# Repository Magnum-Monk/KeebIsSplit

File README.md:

### Keeb Is Split

#### Whats the big idea? (TLDR)
Robust, decent-looking, comfortable, cost-effective, easy-to-build/repair/use 3x6 split keyboard. 

#### References / Credits / Inspirations :
- [**CRKBD**](https://github.com/foostan/crkbd) - all-time classic, "industry standart" of DIY ergo keyboards at this point, if I could say so myself;
- [**Cantor/Piantor**](https://github.com/diepala/cantor) - excellent thumb cluster, overall big improvement in layout ergonimics imo.
- [**Altair/Altair-X**](https://www.reddit.com/r/MechanicalKeyboards/comments/1cg4ejp/gb_altairx_live_now_a_premium_easy_to_learn/) - top grade aestethics, build quality.
- [**Cheapino**](https://github.com/tompi/cheapino) - Robust, easy to assemble, easy to fix/repair, easy to source components, well... cheap! ☺️

#### Firmware
This build utilizes exact pinout that **CRKBD** uses. So you can safely use your Corne (v2/v3) firmware to flash this keyboard.
If you've never had a Corne keyboard before, [this](https://github.com/fathulfahmy/corne-keyboard/tree/main/firmware) should work

#### Build guide 
[here](https://github.com/Magnum-Monk/KeebIsSplit/blob/main/DOC/build_guide.md)

#### BOM
| Part                 | Amount | Links                                                                                                                                                                                                                                                                                                                                                    |
|----------------------|--------|----------------------------------------------------------------------------------------------------------------------------------------------------------------------------------------------------------------------------------------------------------------------------------------------------------------------------------------------------------|
| ProMicro-like MCU    | 2      | [aliexpress](https://aliexpress.com/item/1005004242820623.html?spm=a2g2w.orderdetail.0.0.460d4aa6AvOP5C&sku_id=12000028500661497)                                                                                                                                                                                                            |
| PCB                  | 2      | JLCPCB, PCBWay or other service that you prefer                                                                                                                                                                                                                                                                                                          |
| MX HotSwap Socket    | 42     | [aliexpress](https://aliexpress.com/wholesale?SearchText=kailh+mx+socket&g=y&page=1&searchInfo=A6ON%2FDUCyFd0j2HDxpeVKVoOMc2j+7O64tYNu5a8P+V8gMksvBOiUL7krwlUwZ266w1Qflck+JXe18xAFwbaMovdHjI2%2F2ouiiGyMe3C3O8S2CPD%2Fw7SRsXFQPxfUhNKvHtfjXIBBqE1jemlzqPQiXWU4ihS99yHB8lfgTvQgW8j1PY5epuYAnrB)                                                                          |
| SMD SOD123 Diode     | 42     | [aliexpress](https://www.aliexpress.com/w/wholesale-sod-123-1n4148.html?spm=a2g0o.detail.auto_suggest.3.49e124bT24bTMs)                                                                                                                                                                                                                                       |
| USB-A Socket         | 2      | [aliexpress](https://aliexpress.com/item/1005006501690133.html?sku_id=12000037434446990&spm=a2g2w.productlist.search_results.12.5a9f44b6SVPu5b)                                                                                                                                                                                                                         |
| USB-A -> USB-A Cable | 1      | [aliexpress 1](https://aliexpress.com/item/1005003574732583.html?spm=a2g2w.orderdetail.0.0.44344aa6HsNdnS&sku_id=12000026341806398) [aliexpress 2](https://aliexpress.com/item/1005006002851777.html?spm=a2g2w.orderdetail.0.0.312e4aa6oU8xds&sku_id=12000035266036584)  [aliexpress 3](https://aliexpress.com/item/1005007351594401.html?spm=a2g2w.orderdetail.0.0.4f0d4aa6ib4thb&sku_id=12000040385973360)     |
| Reset Button         | 2      | [aliexpress](https://aliexpress.com/item/1005007177692594.html?sku_id=12000039712603251&spm=a2g2w.productlist.search_results.11.2bad61e4nLrZqG)                                                                                                                                                                                                                         |
| Header Pin Sockets (20 pin)    | 4      | [aliexpress](https://aliexpress.com/item/1005005104952508.html?sku_id=12000031676025007&spm=a2g2w.productlist.search_results.13.42b445bb9N34Mz)                                                                                                                                                                                                                         |
| M2x5 screw           | 20     | For attaching mounting plate and bottom case                                                                                                                                                                                                                                                                                                                                                         |
| M2x6 screw           | 8      | For attaching top case to bottom case |
| M2x5 spacer          | 18     | [aliexpress](https://aliexpress.com/item/4000314663724.html?sku_id=10000001297126740&spm=a2g2w.productlist.search_results.0.67825d52ElIZ9D)                                                                                                                                                                                                                             |
| Top case left           | 1      | |
| Top case right          | 1      | |
| Bottom case left        | 1      | |
| Bottom case right       | 1      | |
| Mounting plate left     | 1      | |
| Mounting plate right    | 1      | |
| Foam mid                | 2      | |
| Foam bottom             | 2      | |

#### "Why won't you just use one of those referenced options?"
(Basically, a list of nit-picks 😀 )
- **CRKBD** - thumb cluster, specifically 1.5u outermost keys. Not only does it feel a bit clunky for me to use, but also, finding matching keycaps for those keys could be challenging and annoying (and convex 1.5u spacebar is a rarity of its own kind). Although I do somewhat understand the reasoning behind this (design-wise, it makes sense to extend this key to 1.5u, because with 1u you kind of have this "weird" empty corner between this key and the MCU, which for some may look off-putting. Since the mcu is quite wide, you cannot eliminate this issue without moving the whole cluster outwards or rotating it in a werid position, which in and of itself could hurt comfort of use. TRRS connection between two halves.
> Since TRRS safety is quite sensitive and reoccuring topic in the DIY-keyboards community I will not touch it here (or will I?), but I would avoid this option if possible.

- **Cantor / Piantor** - although it is very comfortable to use layout-wise, the MCU board itself is huge, albeit much easier to flash. Which in turn somewhat leaves it with the only option for the halves connection to also be TRRS.
- **Altair/Altair-X** - Not open source. Difficult to repair, if something "dies".  Good luck finding available one to buy these days 😀, not to mention hefty price tag.
- **Cheapino** - RJ45 might be too janky-looking and overall big connector for some users (me included), Otherwise very cool and build-friendly board 🥰.

#### Why not low-profile?

Well, mostly the switches. I am yet to find LP switch, that can compete in typing feel with some remarkable and widely loved MX-type ones. And I have tried almost all chocs, a variety of KS33 and Kailh LP models. The available selection of MX switches at this point is far more superior imo, and could fulfill the needs of any enthusiast. 

#### Why not wireless?
I've tried multiple wireless keyboards, and keeping their charge levels in check is just another hassle for me. And the batteries themselves being another point of failure (experienced quite a few "spicy pillows" myself), which defeats the goal of this being robust. Maybe in the future I'll rethink this, but with the use of 3.7v AAA or coin cell batteries as a power source.

#### Why no LEDs?
I mean... Nothing against it, but it adds nothing of value to the device imo, except, well, cost and build complexity.

#### Why no OLEDs?
Again, I fiddled with them for some time in my Corne keyboards, but at the end I just removed them for the purpose of fitting in a slimmer case. How often do you look at them anyway, while using your device? They're okay to help debugging some build issues with the keyboard, but other than than, just "bells and whistles".

#### Why USB-A connectors? (Oops, I couldn't help myself)

Although its highly debatable, I still think this is the "safe-ish" option to connect two halves of a keyboard:
- Hot pluggable. Finally, no fear of accidentally detaching the cable from your keyboard and frying GPIO, or the whole MCU.
- Low-ish chance of connecting it to the wrong device accidentally, since finding spare USB-A to USB-A cable lying on your desk, connected to some of your devices is highly unlikely (not the case with USB-c, for example). Not to mention, using the same port type to connect keyboard to PC and left MCU to the right MCU can be somewhat confusing, and could easily result in  some MCU damage, being connected improperly).

> But still, please do not use USB-A port on this keyboard to anything other than connecting two halves together. Connecting it to, say, USB port on your PC would most likely damage your MCU, since standard USB port supplies 5v, and MCU is expecting 3.3v.

- Although the selection of available cables is much more limited, than, say, TRRS, there are a lot of options still. And If nothing fits your bill, there are a lot of connectors available to build your own custom cable.

Overall, designing circuitry that supports bi-directional data/power flow with reliable and resilient MCU protection is a challenging task (quite beyond my expertise, tbh), and will definitely significantly complicate assembling process and increase the amount of parts needed (and the price, which is definitely an important factor too).

#### KiCad symbol/footprint libraries used:
- Mostly [scottokeebs](https://github.com/joe-scotto/scottokeebs/tree/main "scottokeebs") ones. Huge props to the guy!
- Also [foostan's](https://github.com/foostan/kbd/tree/f90510c11b6df53bcdb55740b0d59183957e4036) ones

Unfortunately, all 3D files are made in SolidWorks, which is not free/opensource. Maybe someday I'll redo them in FreeCad, but for now it is what it is. STP files for 3D printing (which most slicers should support nowadays) are also included.

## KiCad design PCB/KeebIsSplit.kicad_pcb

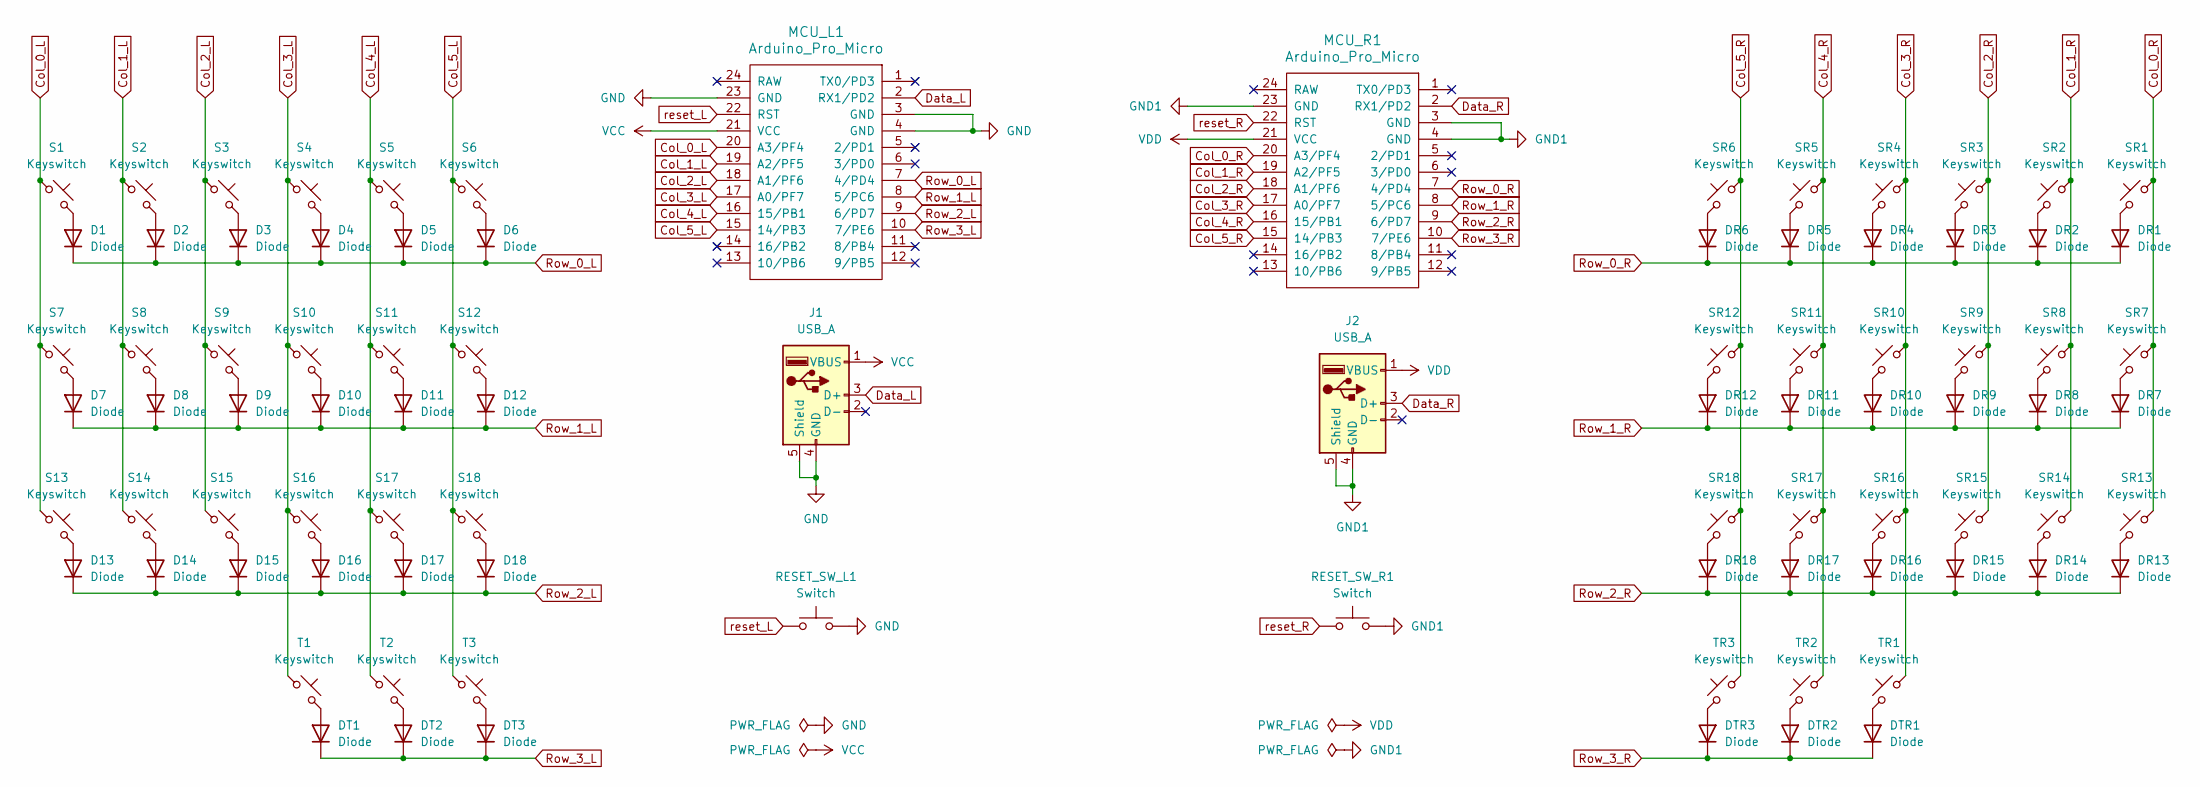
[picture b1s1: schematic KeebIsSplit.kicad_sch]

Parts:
D1, D2, D3, D4, D5, D6, D7, D8, D9, D10, D11, D12, D13, D14, D15, D16, D17, D18: Diode; Diode_SOD-123
DR1, DR2, DR3, DR4, DR5, DR6, DR7, DR8, DR9, DR10, DR11, DR12, DR13, DR14, DR15, DR16, DR17, DR18: Diode; Diode_SOD-123
DT1, DT2, DT3: Diode; Diode_SOD-123
DTR1, DTR2, DTR3: Diode; Diode_SOD-123
J1, J2: USB_A; USB_A_Molex_67643_Horizontal
MCU_L1: Arduino_Pro_Micro
MCU_R1: Arduino_Pro_Micro
RESET_SW_L1: Switch; Button_MJTP1243
RESET_SW_R1: Switch; Button_MJTP1243
S1, S2, S3, S4, S5, S6, S7, S8, S9, S10, S11, S12, S13, S14, S15, S16, S17, S18: Keyswitch; Hotswap_MX_1.00u
SR1, SR2, SR3, SR4, SR5, SR6, SR7, SR8, SR9, SR10, SR11, SR12, SR13, SR14, SR15, SR16, SR17, SR18: Keyswitch; Hotswap_MX_1.00u
T1, T2, T3: Keyswitch; Hotswap_MX_1.00u
TR1, TR2, TR3: Keyswitch; Hotswap_MX_1.00u

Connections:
Col_0_L: MCU_L1.20 (A3/PF4), S1.1, S7.1, S13.1
Col_0_R: MCU_R1.20 (A3/PF4), SR1.1, SR7.1, SR13.1
Col_1_L: MCU_L1.19 (A2/PF5), S2.1, S8.1, S14.1
Col_1_R: MCU_R1.19 (A2/PF5), SR2.1, SR8.1, SR14.1
Col_2_L: MCU_L1.18 (A1/PF6), S3.1, S9.1, S15.1
Col_2_R: MCU_R1.18 (A1/PF6), SR3.1, SR9.1, SR15.1
Col_3_L: MCU_L1.17 (A0/PF7), S4.1, S10.1, S16.1, T1.1
Col_3_R: MCU_R1.17 (A0/PF7), SR4.1, SR10.1, SR16.1, TR1.1
Col_4_L: MCU_L1.16 (15/PB1), S5.1, S11.1, S17.1, T2.1
Col_4_R: MCU_R1.16 (15/PB1), SR5.1, SR11.1, SR17.1, TR2.1
Col_5_L: MCU_L1.15 (14/PB3), S6.1, S12.1, S18.1, T3.1
Col_5_R: MCU_R1.15 (14/PB3), SR6.1, SR12.1, SR18.1, TR3.1
Data_L: J1.3 (D+), MCU_L1.2 (RX1/PD2)
Data_R: J2.3 (D+), MCU_R1.2 (RX1/PD2)
GND: J1.4 (GND), J1.5 (Shield), MCU_L1.3 (GND), MCU_L1.4 (GND), MCU_L1.23 (GND), RESET_SW_L1.2
GND1: J2.4 (GND), J2.5 (Shield), MCU_R1.3 (GND), MCU_R1.4 (GND), MCU_R1.23 (GND), RESET_SW_R1.2
unnamed: D1.2 (A), S1.2
unnamed: D2.2 (A), S2.2
unnamed: D3.2 (A), S3.2
unnamed: D4.2 (A), S4.2
unnamed: D5.2 (A), S5.2
unnamed: D6.2 (A), S6.2
unnamed: D7.2 (A), S7.2
unnamed: D8.2 (A), S8.2
unnamed: D9.2 (A), S9.2
unnamed: D10.2 (A), S10.2
unnamed: D11.2 (A), S11.2
unnamed: D12.2 (A), S12.2
unnamed: D13.2 (A), S13.2
unnamed: D14.2 (A), S14.2
unnamed: D15.2 (A), S15.2
unnamed: D16.2 (A), S16.2
unnamed: D17.2 (A), S17.2
unnamed: D18.2 (A), S18.2
unnamed: DR1.2 (A), SR1.2
unnamed: DR2.2 (A), SR2.2
unnamed: DR3.2 (A), SR3.2
unnamed: DR4.2 (A), SR4.2
unnamed: DR5.2 (A), SR5.2
unnamed: DR6.2 (A), SR6.2
unnamed: DR7.2 (A), SR7.2
unnamed: DR8.2 (A), SR8.2
unnamed: DR9.2 (A), SR9.2
unnamed: DR10.2 (A), SR10.2
unnamed: DR11.2 (A), SR11.2
unnamed: DR12.2 (A), SR12.2
unnamed: DR13.2 (A), SR13.2
unnamed: DR14.2 (A), SR14.2
unnamed: DR15.2 (A), SR15.2
unnamed: DR16.2 (A), SR16.2
unnamed: DR17.2 (A), SR17.2
unnamed: DR18.2 (A), SR18.2
unnamed: DT1.2 (A), T1.2
unnamed: DT2.2 (A), T2.2
unnamed: DT3.2 (A), T3.2
unnamed: DTR1.2 (A), TR1.2
unnamed: DTR2.2 (A), TR2.2
unnamed: DTR3.2 (A), TR3.2
Row_0_L: D1.1 (K), D2.1 (K), D3.1 (K), D4.1 (K), D5.1 (K), D6.1 (K), MCU_L1.7 (4/PD4)
Row_0_R: DR1.1 (K), DR2.1 (K), DR3.1 (K), DR4.1 (K), DR5.1 (K), DR6.1 (K), MCU_R1.7 (4/PD4)
Row_1_L: D7.1 (K), D8.1 (K), D9.1 (K), D10.1 (K), D11.1 (K), D12.1 (K), MCU_L1.8 (5/PC6)
Row_1_R: DR7.1 (K), DR8.1 (K), DR9.1 (K), DR10.1 (K), DR11.1 (K), DR12.1 (K), MCU_R1.8 (5/PC6)
Row_2_L: D13.1 (K), D14.1 (K), D15.1 (K), D16.1 (K), D17.1 (K), D18.1 (K), MCU_L1.9 (6/PD7)
Row_2_R: DR13.1 (K), DR14.1 (K), DR15.1 (K), DR16.1 (K), DR17.1 (K), DR18.1 (K), MCU_R1.9 (6/PD7)
Row_3_L: DT1.1 (K), DT2.1 (K), DT3.1 (K), MCU_L1.10 (7/PE6)
Row_3_R: DTR1.1 (K), DTR2.1 (K), DTR3.1 (K), MCU_R1.10 (7/PE6)
VCC: J1.1 (VBUS), MCU_L1.21 (VCC)
VDD: J2.1 (VBUS), MCU_R1.21 (VCC)
reset_L: MCU_L1.22 (RST), RESET_SW_L1.1
reset_R: MCU_R1.22 (RST), RESET_SW_R1.1

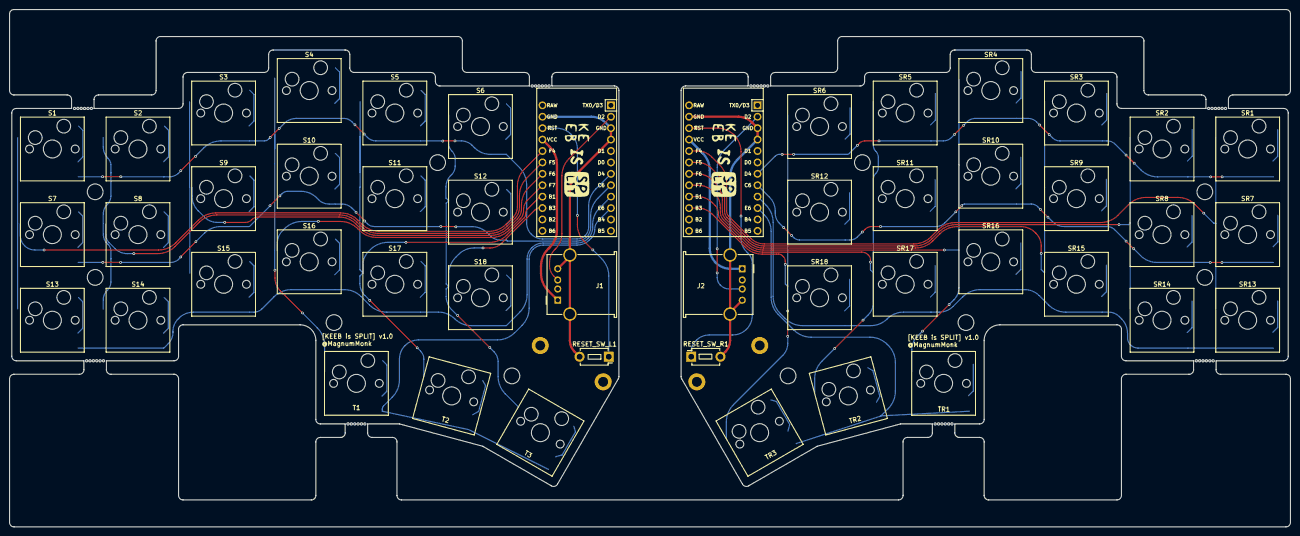
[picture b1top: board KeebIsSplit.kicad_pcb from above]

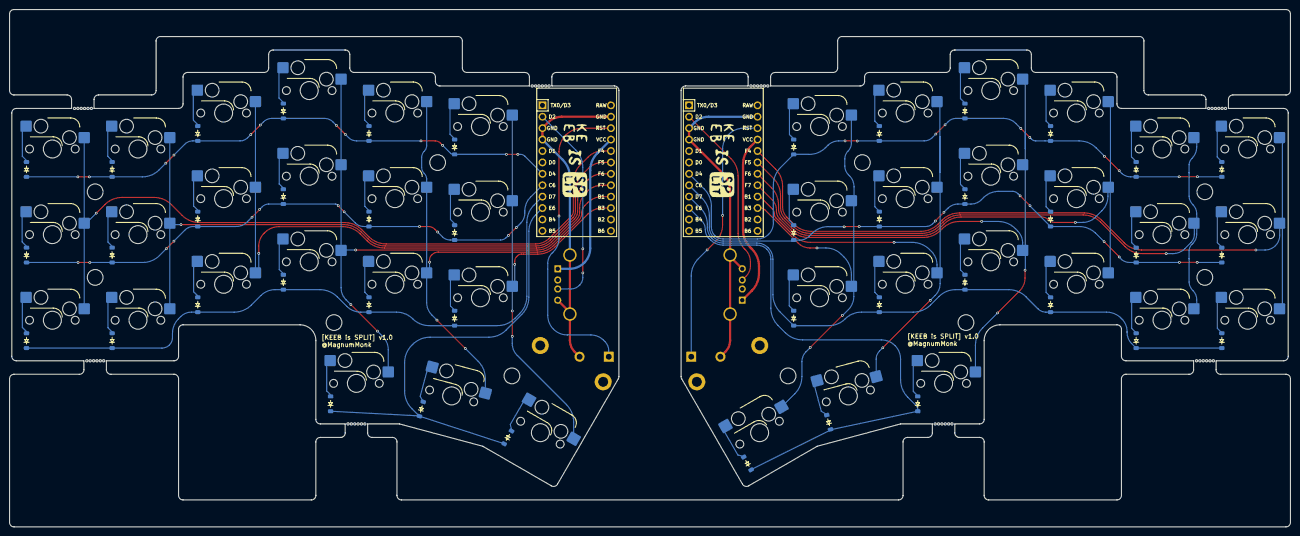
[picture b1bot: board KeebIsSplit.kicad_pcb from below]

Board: 2 copper layers, 285.0 x 115.1 mm, 90 parts (44 on the bottom side), 70 nets.

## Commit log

2025-03-03 Add PCB files
2025-03-03 Add Gerber files
2025-03-03 Add 3D files
2025-03-03 Remove TMP files
2025-03-03 Add an initial README
2025-03-03 Edit README
2025-03-04 Add 3D models of MX switches with keycaps
2025-03-04 Add keys to thumb cluster in assembly
2025-03-23 add some assets
2025-03-23 Update build guide
2025-03-23 fix some aliexpress links
2025-03-28 Increase the MX mounting hole by .1mm
2025-03-28 Update the assembly
